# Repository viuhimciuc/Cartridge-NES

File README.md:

# 🎮 Nintendo Entertainment System (NES) Cartridge PCBs

An open-source collection of hardware design files and schematics for custom, functional **Nintendo Entertainment System (NES)** cartridge printed circuit boards (PCBs), using the [SST39SF010A](https://www.microchip.com/en-us/product/sst39sf010a), [SST39SF020A](https://www.microchip.com/en-us/product/sst39sf020a), [SST39SF040](https://www.microchip.com/en-us/product/sst39sf040) memory chip. This repository includes boards based on original discrete logic designs, advanced memory management controllers (MMCs), and mask ROM replacement utilities created inside **KiCad**.

---

## 📂 Repository Structure

The project organizes board designs by memory mapper architectures and utility profiles:

*   **📁 `Discrete logic boards using`** – Simple mapper solutions utilizing standard 74-series logic chips (e.g., AxROM, UxROM, NROM configurations).
*   **📁 `MMC1 boards NES-SxROM`** – Designs compatible with the Nintendo **MMC1** ASIC mapper family supporting multi-directional scrolling and battery-backed saves.
*   **📁 `MMC3 boards NES-TxROM`** – Performance configurations adapting the highly versatile **MMC3** ASIC architecture for scanline IRQ counters and larger ROM sizes.
*   **📁 `NES MASK ROM`** – Hardware breakout and adapter boards targeting pin-compatible conversions from modern Flash/EPROM/EEPROM chips to original NES hardware slots.
*   **📊 Documentation Assets:**
    *   `Mappers.xls` – Comparison matrices tracking hardware compatibility, signaling, and line configurations.
    *   `pin_MMC3.xls` – Precision mapping registers and Pinout details targeting the MMC3 layout.

---

## 📸 PCB Gallery

<p align="center">

</p>

---

## 🛠️ Getting Started & Manufacturing

### Prerequisites
1. Download and set up the stable branch of [KiCad EDA](https://kicad.org/).
2. Standard interactive hardware tools (soldering iron, multi-meter, flux).

### Cloning the Project
```bash
git clone https://github.com/viuhimciuc/Cartridge-NES.git
cd Cartridge-NES
```

### Exporting Gerbers for PCB Production
1. Launch **KiCad** and open the `.kicad_pcb` layout file from the directory matching your board configuration.
2. Navigate to **File** ➡️ **Plot...**
3. Select **Gerber** as the output configuration format.
4. Specify target layers (typically *F.Cu*, *B.Cu*, *F.Paste*, *B.Paste*, *F.Silkscreen*, *B.Silkscreen*, *F.Mask*, *B.Mask*, and *Edge.Cuts*).
5. Choose **Generate Drill Files...** using standard Exxon/Drill configurations.
6. Package all generated artifacts into a single `.zip` archive.
7. Upload the container directly to production fabs like [JLCPCB](https://jlcpcb.com/) or [PCBWay](https://www.pcbway.com/).

---

## 🤝 Contributing & Support

Contributions addressing trace corrections, optimized routing patterns, or alternative flash memory compatibility layouts are welcome! 

1. **Fork** this repository.
2. Build an active feature/fix branch (`git checkout -b feature/AmazingFeature`).
3. Commit structural modifications (`git commit -m 'Add support for unique flash footprints'`).
4. **Push** the configuration branch (`git push origin feature/AmazingFeature`).
5. Open a **Pull Request**.

---

## 📜 License

Distributed under the **MIT License**. Check out the accompanying `.gitignore` configuration for setup parameters.

---
<p align="center">Made with ❤️ for retro console preservation.</p>

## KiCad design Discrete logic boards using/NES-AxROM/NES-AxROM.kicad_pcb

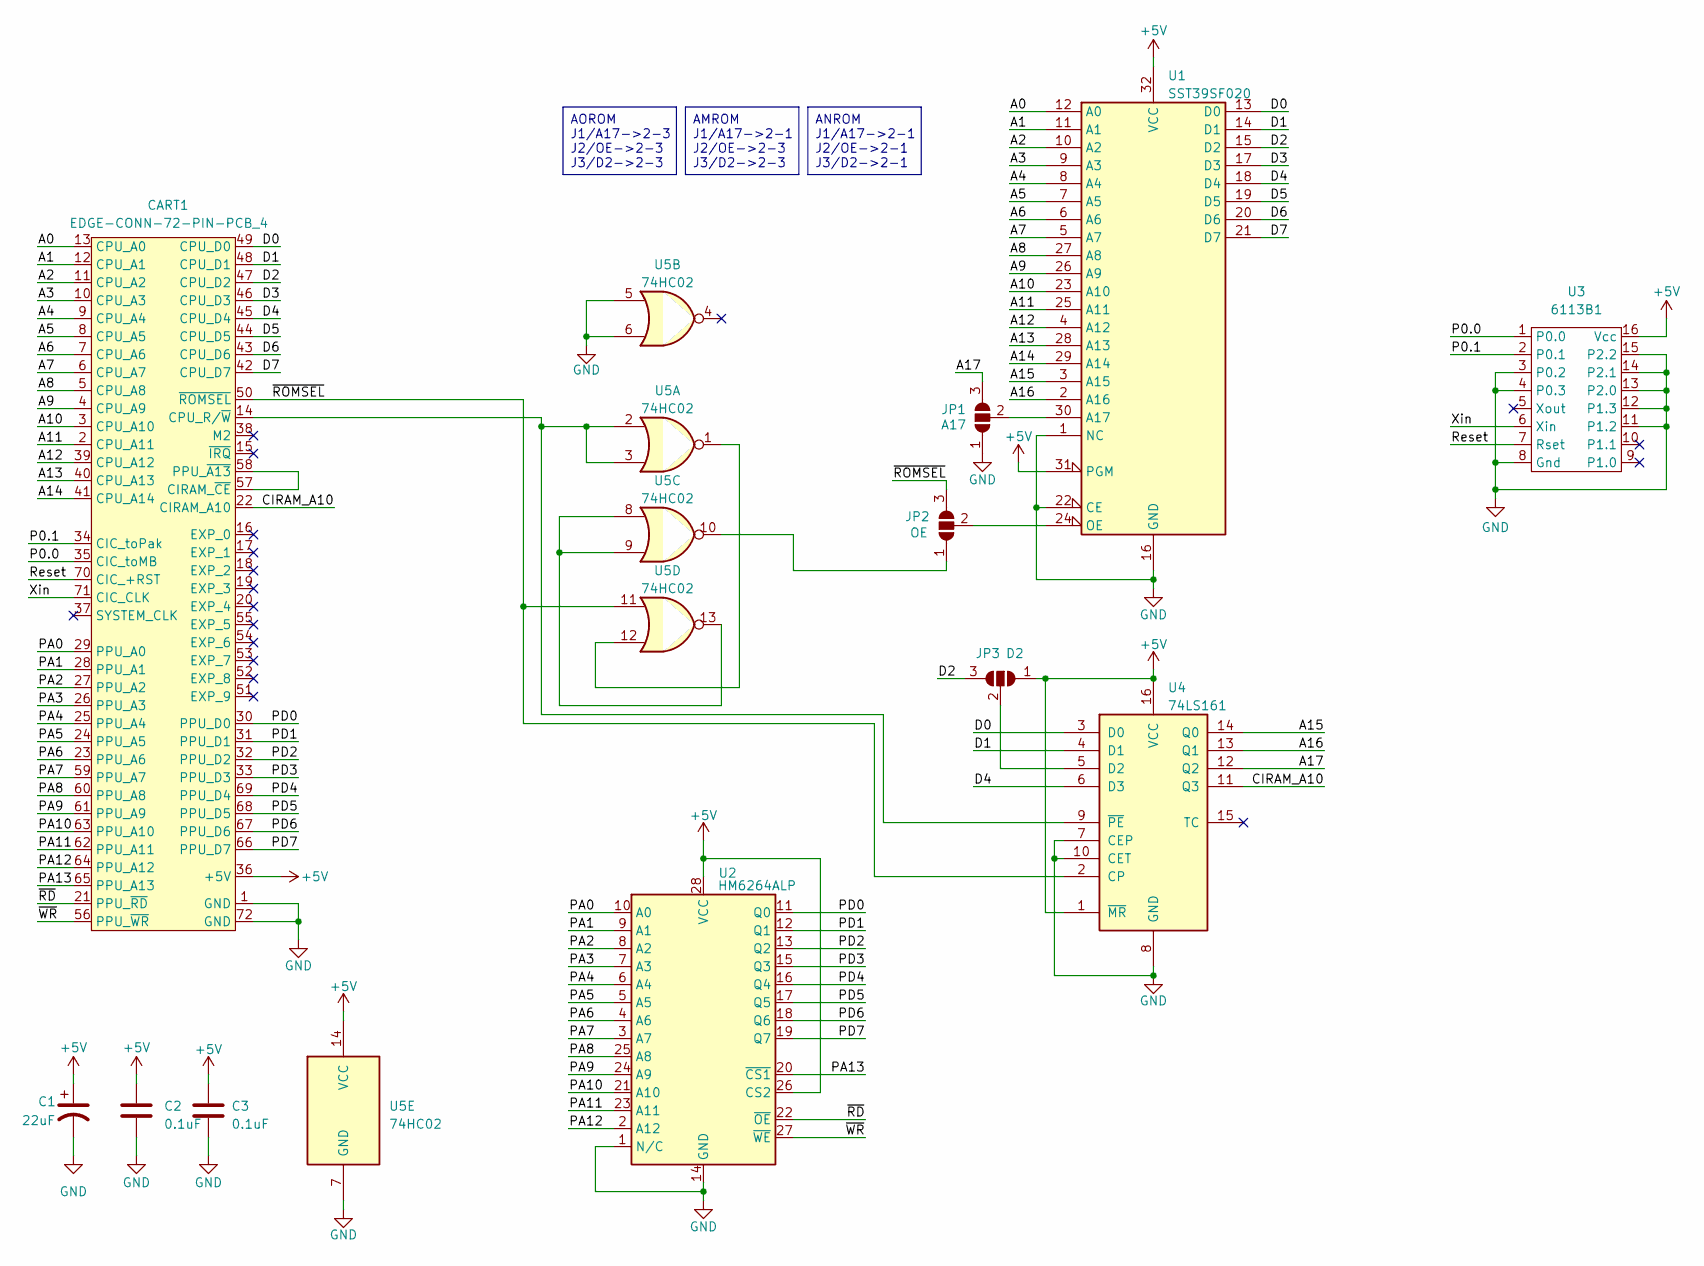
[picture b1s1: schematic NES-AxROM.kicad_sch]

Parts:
C1: 22uF; CP_Radial_D4.0mm_P2.00mm
C2, C3: 0.1uF; C_Axial_P7.5mm_P2.50mm
CART1: EDGE-CONN-72-PIN-PCB_4; PCB_4-CART-72-2.50-CONN
JP1: A17; SolderJumper-3_P1.3mm_Open_RoundedPad1.0x1.5mm_NumberLabels
JP2: OE; SolderJumper-3_P1.3mm_Open_RoundedPad1.0x1.5mm_NumberLabels
JP3: D2; SolderJumper-3_P1.3mm_Open_RoundedPad1.0x1.5mm_NumberLabels
U1: SST39SF020; DIP-32_W15.24mm
U2: HM6264ALP; DIP-28_W15.24mm
U3: 6113B1; DIP-16_W7.62mm
U4: 74LS161; DIP-16_W7.62mm
U5: 74HC02; DIP-14_W7.62mm

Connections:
+5V: C1.1, C2.1, C3.1, CART1.36 (+5V), JP3.1 (A), U1.31 (PGM), U1.32 (VCC), U2.26 (CS2), U2.28 (VCC), U3.16 (Vcc), U4.1 (~MR), U4.16 (VCC), U5.14 (VCC)
/A0: CART1.13 (CPU_A0), U1.12 (A0)
/A1: CART1.12 (CPU_A1), U1.11 (A1)
/A2: CART1.11 (CPU_A2), U1.10 (A2)
/A3: CART1.10 (CPU_A3), U1.9 (A3)
/A4: CART1.9 (CPU_A4), U1.8 (A4)
/A5: CART1.8 (CPU_A5), U1.7 (A5)
/A6: CART1.7 (CPU_A6), U1.6 (A6)
/A7: CART1.6 (CPU_A7), U1.5 (A7)
/A8: CART1.5 (CPU_A8), U1.27 (A8)
/A9: CART1.4 (CPU_A9), U1.26 (A9)
/A10: CART1.3 (CPU_A10), U1.23 (A10)
/A11: CART1.2 (CPU_A11), U1.25 (A11)
/A12: CART1.39 (CPU_A12), U1.4 (A12)
/A13: CART1.40 (CPU_A13), U1.28 (A13)
/A14: CART1.41 (CPU_A14), U1.29 (A14)
/A15: U1.3 (A15), U4.14 (Q0)
/A16: U1.2 (A16), U4.13 (Q1)
/A17: JP1.3 (B), U4.12 (Q2)
/CIRAM_A10: CART1.22 (CIRAM_A10), U4.11 (Q3)
/D0: CART1.49 (CPU_D0), U1.13 (D0), U4.3 (D0)
/D1: CART1.48 (CPU_D1), U1.14 (D1), U4.4 (D1)
/D2: CART1.47 (CPU_D2), JP3.3 (B), U1.15 (D2)
/D3: CART1.46 (CPU_D3), U1.17 (D3)
/D4: CART1.45 (CPU_D4), U1.18 (D4), U4.6 (D3)
/D5: CART1.44 (CPU_D5), U1.19 (D5)
/D6: CART1.43 (CPU_D6), U1.20 (D6)
/D7: CART1.42 (CPU_D7), U1.21 (D7)
/P0.0: CART1.35 (CIC_toMB), U3.1 (P0.0)
/P0.1: CART1.34 (CIC_toPak), U3.2 (P0.1)
/PA0: CART1.29 (PPU_A0), U2.10 (A0)
/PA1: CART1.28 (PPU_A1), U2.9 (A1)
/PA2: CART1.27 (PPU_A2), U2.8 (A2)
/PA3: CART1.26 (PPU_A3), U2.7 (A3)
/PA4: CART1.25 (PPU_A4), U2.6 (A4)
/PA5: CART1.24 (PPU_A5), U2.5 (A5)
/PA6: CART1.23 (PPU_A6), U2.4 (A6)
/PA7: CART1.59 (PPU_A7), U2.3 (A7)
/PA8: CART1.60 (PPU_A8), U2.25 (A8)
/PA9: CART1.61 (PPU_A9), U2.24 (A9)
/PA10: CART1.63 (PPU_A10), U2.21 (A10)
/PA11: CART1.62 (PPU_A11), U2.23 (A11)
/PA12: CART1.64 (PPU_A12), U2.2 (A12)
/PA13: CART1.65 (PPU_A13), U2.20 (~CS1)
/PD0: CART1.30 (PPU_D0), U2.11 (Q0)
/PD1: CART1.31 (PPU_D1), U2.12 (Q1)
/PD2: CART1.32 (PPU_D2), U2.13 (Q2)
/PD3: CART1.33 (PPU_D3), U2.15 (Q3)
/PD4: CART1.69 (PPU_D4), U2.16 (Q4)
/PD5: CART1.68 (PPU_D5), U2.17 (Q5)
/PD6: CART1.67 (PPU_D6), U2.18 (Q6)
/PD7: CART1.66 (PPU_D7), U2.19 (Q7)
/Reset: CART1.70 (CIC_+RST), U3.7 (Rset)
/Xin: CART1.71 (CIC_CLK), U3.6 (Xin)
/~RD: CART1.21 (PPU_~RD), U2.22 (~OE)
/~ROMSEL: CART1.50 (~ROMSEL), JP2.3 (B), U4.2 (CP), U5.11
/~WR: CART1.56 (PPU_~WR), U2.27 (~WE)
GND: C1.2, C2.2, C3.2, CART1.1 (GND), CART1.72 (GND), JP1.1 (A), U1.1 (NC), U1.16 (GND), U1.22 (CE), U2.1 (N/C), U2.14 (GND), U3.3 (P0.2), U3.4 (P0.3), U3.8 (Gnd), U3.11 (P1.2), U3.12 (P1.3), U3.13 (P2.0), U3.14 (P2.1), U3.15 (P2.2), U4.7 (CEP), U4.8 (GND), U4.10 (CET), U5.5, U5.6, U5.7 (GND)
unnamed: CART1.57 (CIRAM_~CE), CART1.58 (PPU_~A13)
unnamed: CART1.14 (CPU_R/~W), U4.9 (~PE), U5.2, U5.3
unnamed: JP1.2 (C), U1.30 (A17)
unnamed: JP2.1 (A), U5.10
unnamed: JP2.2 (C), U1.24 (OE)
unnamed: JP3.2 (C), U4.5 (D2)
unnamed: U5.1, U5.12
unnamed: U5.8, U5.9, U5.13

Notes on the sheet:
AMROM J1/A17->2-1 J2/OE->2-3 J3/D2->2-3
ANROM J1/A17->2-1 J2/OE->2-1 J3/D2->2-1
AOROM J1/A17->2-3 J2/OE->2-3 J3/D2->2-3

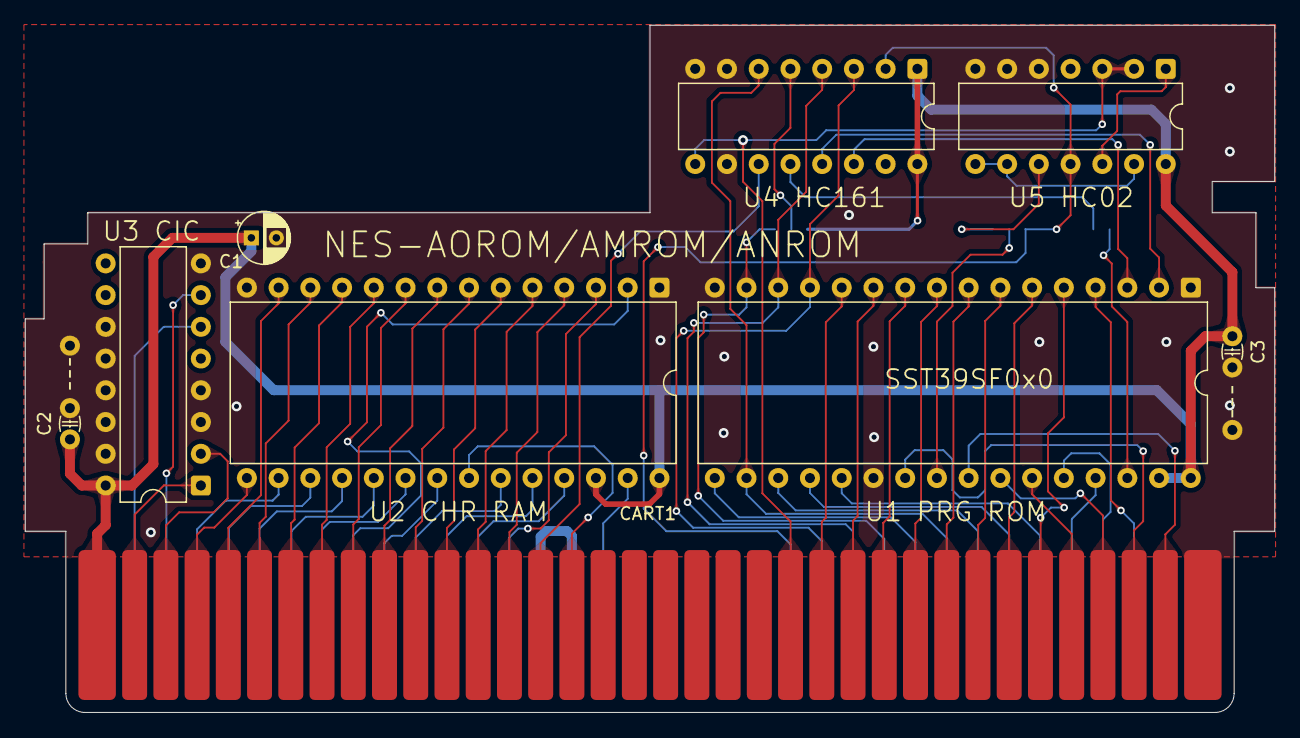
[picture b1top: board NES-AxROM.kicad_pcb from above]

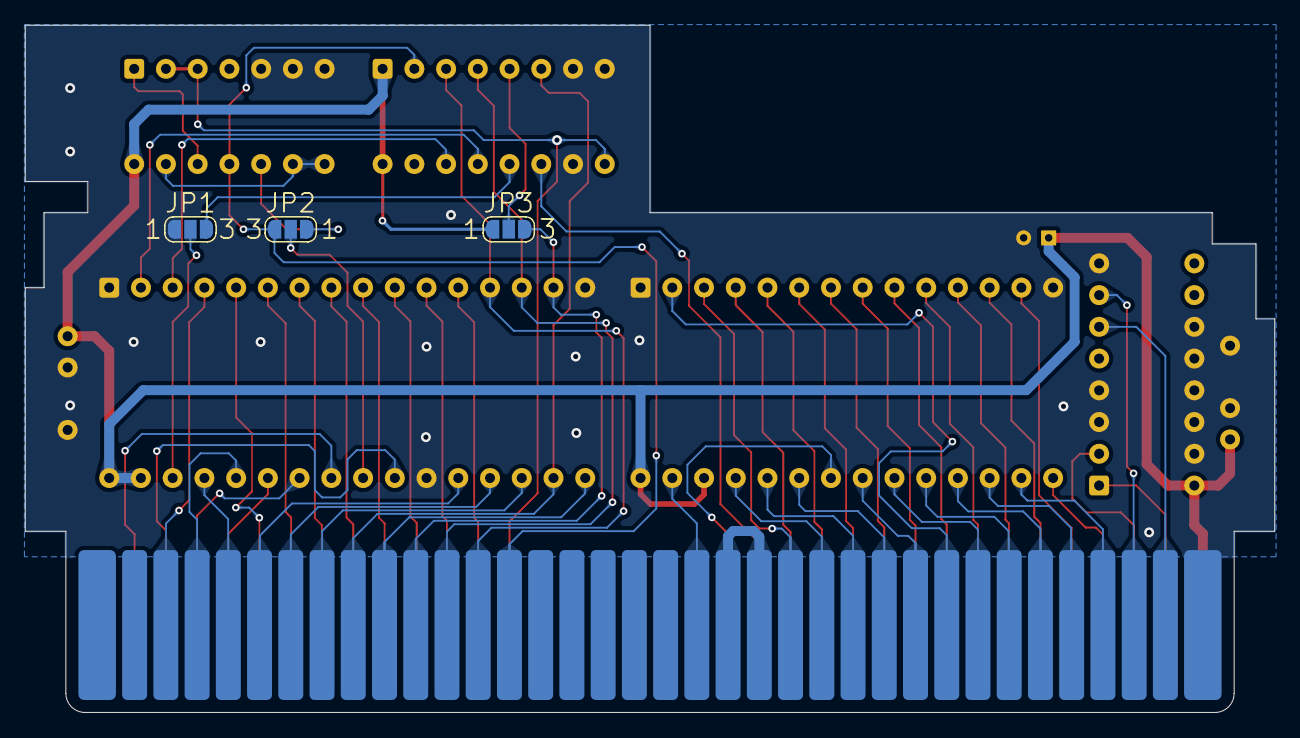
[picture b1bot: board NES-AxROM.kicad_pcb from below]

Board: 2 copper layers, 100.0 x 55.0 mm, 12 parts (3 on the bottom side), 66 nets.

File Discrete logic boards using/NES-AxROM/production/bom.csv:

Designator,Footprint,Quantity,Value,LCSC Part #
C1,CP_Radial_D4.0mm_P2.00mm,1,22uF,
"C2, C3",C_Axial_P7.5mm_P2.50mm,2,0.1uF,
CART1,PCB_4-CART-72-2.50-CONN,1,EDGE-CONN-72-PIN-PCB_4,
JP1,SolderJumper-3_P1.3mm_Open_RoundedPad1.0x1.5mm_NumberLabels,1,A17,
JP2,SolderJumper-3_P1.3mm_Open_RoundedPad1.0x1.5mm_NumberLabels,1,OE,
JP3,SolderJumper-3_P1.3mm_Open_RoundedPad1.0x1.5mm_NumberLabels,1,D2,
U1,DIP-32_W15.24mm,1,SST39SF020,
U2,DIP-28_W15.24mm,1,HM6264ALP,
U3,DIP-16_W7.62mm,1,6113B1,
U4,DIP-16_W7.62mm,1,74LS161,
U5,DIP-14_W7.62mm,1,74HC02,

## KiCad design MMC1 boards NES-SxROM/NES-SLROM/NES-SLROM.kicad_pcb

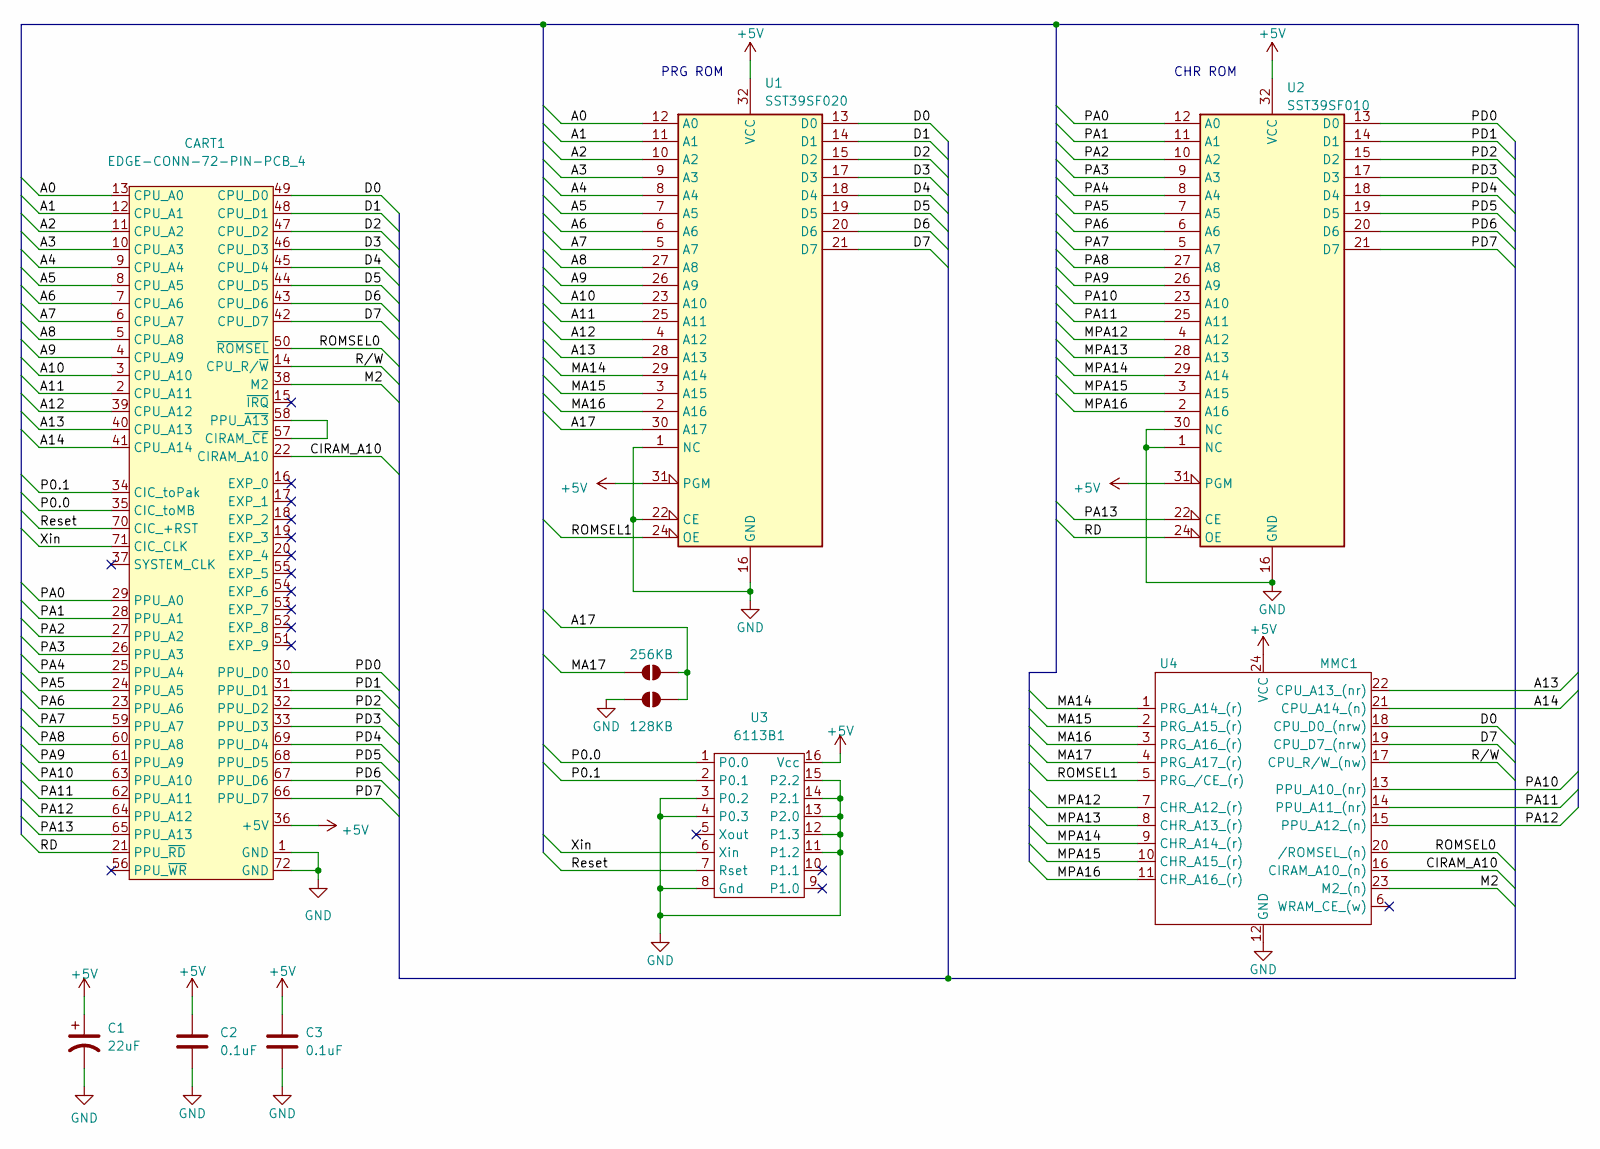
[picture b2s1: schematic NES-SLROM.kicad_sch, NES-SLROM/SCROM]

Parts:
C1: 22uF; CP_Radial_D4.0mm_P1.50mm
C2, C3: 0.1uF; C_Disc_D3.0mm_W1.6mm_P2.50mm
CART1: EDGE-CONN-72-PIN-PCB_4; PCB_4-CART-72-2.50-CONN
JP1: 256KB; SolderJumper-2_P1.3mm_Open_RoundedPad1.0x1.5mm
JP2: 128KB; SolderJumper-2_P1.3mm_Open_RoundedPad1.0x1.5mm
U1: SST39SF020; DIP-32_W15.24mm
U2: SST39SF010; DIP-32_W15.24mm
U3: 6113B1; DIP-16_W7.62mm
U4: MMC1; DIP-24_W7.62mm_Pads_1.78mm

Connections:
+5V: C1.1, C2.1, C3.1, CART1.36 (+5V), U1.31 (PGM), U1.32 (VCC), U2.31 (PGM), U2.32 (VCC), U3.16 (Vcc), U4.24 (VCC)
/A0: CART1.13 (CPU_A0), U1.12 (A0)
/A1: CART1.12 (CPU_A1), U1.11 (A1)
/A2: CART1.11 (CPU_A2), U1.10 (A2)
/A3: CART1.10 (CPU_A3), U1.9 (A3)
/A4: CART1.9 (CPU_A4), U1.8 (A4)
/A5: CART1.8 (CPU_A5), U1.7 (A5)
/A6: CART1.7 (CPU_A6), U1.6 (A6)
/A7: CART1.6 (CPU_A7), U1.5 (A7)
/A8: CART1.5 (CPU_A8), U1.27 (A8)
/A9: CART1.4 (CPU_A9), U1.26 (A9)
/A10: CART1.3 (CPU_A10), U1.23 (A10)
/A11: CART1.2 (CPU_A11), U1.25 (A11)
/A12: CART1.39 (CPU_A12), U1.4 (A12)
/A13: CART1.40 (CPU_A13), U1.28 (A13), U4.22 (CPU_A13_(nr))
/A14: CART1.41 (CPU_A14), U4.21 (CPU_A14_(n))
/A17: JP1.1 (A), JP2.1 (A), U1.30 (A17)
/CIRAM_A10: CART1.22 (CIRAM_A10), U4.16 (CIRAM_A10_(n))
/D0: CART1.49 (CPU_D0), U1.13 (D0), U4.18 (CPU_D0_(nrw))
/D1: CART1.48 (CPU_D1), U1.14 (D1)
/D2: CART1.47 (CPU_D2), U1.15 (D2)
/D3: CART1.46 (CPU_D3), U1.17 (D3)
/D4: CART1.45 (CPU_D4), U1.18 (D4)
/D5: CART1.44 (CPU_D5), U1.19 (D5)
/D6: CART1.43 (CPU_D6), U1.20 (D6)
/D7: CART1.42 (CPU_D7), U1.21 (D7), U4.19 (CPU_D7_(nrw))
/M2: CART1.38 (M2), U4.23 (M2_(n))
/MA14: U1.29 (A14), U4.1 (PRG_A14_(r))
/MA15: U1.3 (A15), U4.2 (PRG_A15_(r))
/MA16: U1.2 (A16), U4.3 (PRG_A16_(r))
/MA17: JP1.2 (B), U4.4 (PRG_A17_(r))
/MPA12: U2.4 (A12), U4.7 (CHR_A12_(r))
/MPA13: U2.28 (A13), U4.8 (CHR_A13_(r))
/MPA14: U2.29 (A14), U4.9 (CHR_A14_(r))
/MPA15: U2.3 (A15), U4.10 (CHR_A15_(r))
/MPA16: U2.2 (A16), U4.11 (CHR_A16_(r))
/P0.0: CART1.35 (CIC_toMB), U3.1 (P0.0)
/P0.1: CART1.34 (CIC_toPak), U3.2 (P0.1)
/PA0: CART1.29 (PPU_A0), U2.12 (A0)
/PA1: CART1.28 (PPU_A1), U2.11 (A1)
/PA2: CART1.27 (PPU_A2), U2.10 (A2)
/PA3: CART1.26 (PPU_A3), U2.9 (A3)
/PA4: CART1.25 (PPU_A4), U2.8 (A4)
/PA5: CART1.24 (PPU_A5), U2.7 (A5)
/PA6: CART1.23 (PPU_A6), U2.6 (A6)
/PA7: CART1.59 (PPU_A7), U2.5 (A7)
/PA8: CART1.60 (PPU_A8), U2.27 (A8)
/PA9: CART1.61 (PPU_A9), U2.26 (A9)
/PA10: CART1.63 (PPU_A10), U2.23 (A10), U4.13 (PPU_A10_(nr))
/PA11: CART1.62 (PPU_A11), U2.25 (A11), U4.14 (PPU_A11_(nr))
/PA12: CART1.64 (PPU_A12), U4.15 (PPU_A12_(n))
/PA13: CART1.65 (PPU_A13), U2.22 (CE)
/PD0: CART1.30 (PPU_D0), U2.13 (D0)
/PD1: CART1.31 (PPU_D1), U2.14 (D1)
/PD2: CART1.32 (PPU_D2), U2.15 (D2)
/PD3: CART1.33 (PPU_D3), U2.17 (D3)
/PD4: CART1.69 (PPU_D4), U2.18 (D4)
/PD5: CART1.68 (PPU_D5), U2.19 (D5)
/PD6: CART1.67 (PPU_D6), U2.20 (D6)
/PD7: CART1.66 (PPU_D7), U2.21 (D7)
/RD: CART1.21 (PPU_~RD), U2.24 (OE)
/ROMSEL0: CART1.50 (~ROMSEL), U4.20 (/ROMSEL_(n))
/ROMSEL1: U1.24 (OE), U4.5 (PRG_/CE_(r))
/Reset: CART1.70 (CIC_+RST), U3.7 (Rset)
/R/W: CART1.14 (CPU_R/~W), U4.17 (CPU_R/W_(nw))
/Xin: CART1.71 (CIC_CLK), U3.6 (Xin)
GND: C1.2, C2.2, C3.2, CART1.1 (GND), CART1.72 (GND), JP2.2 (B), U1.1 (NC), U1.16 (GND), U1.22 (CE), U2.1 (NC), U2.16 (GND), U2.30 (NC), U3.3 (P0.2), U3.4 (P0.3), U3.8 (Gnd), U3.11 (P1.2), U3.12 (P1.3), U3.13 (P2.0), U3.14 (P2.1), U3.15 (P2.2), U4.12 (GND)
unnamed: CART1.57 (CIRAM_~CE), CART1.58 (PPU_~A13)

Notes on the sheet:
PRG ROM
CHR ROM

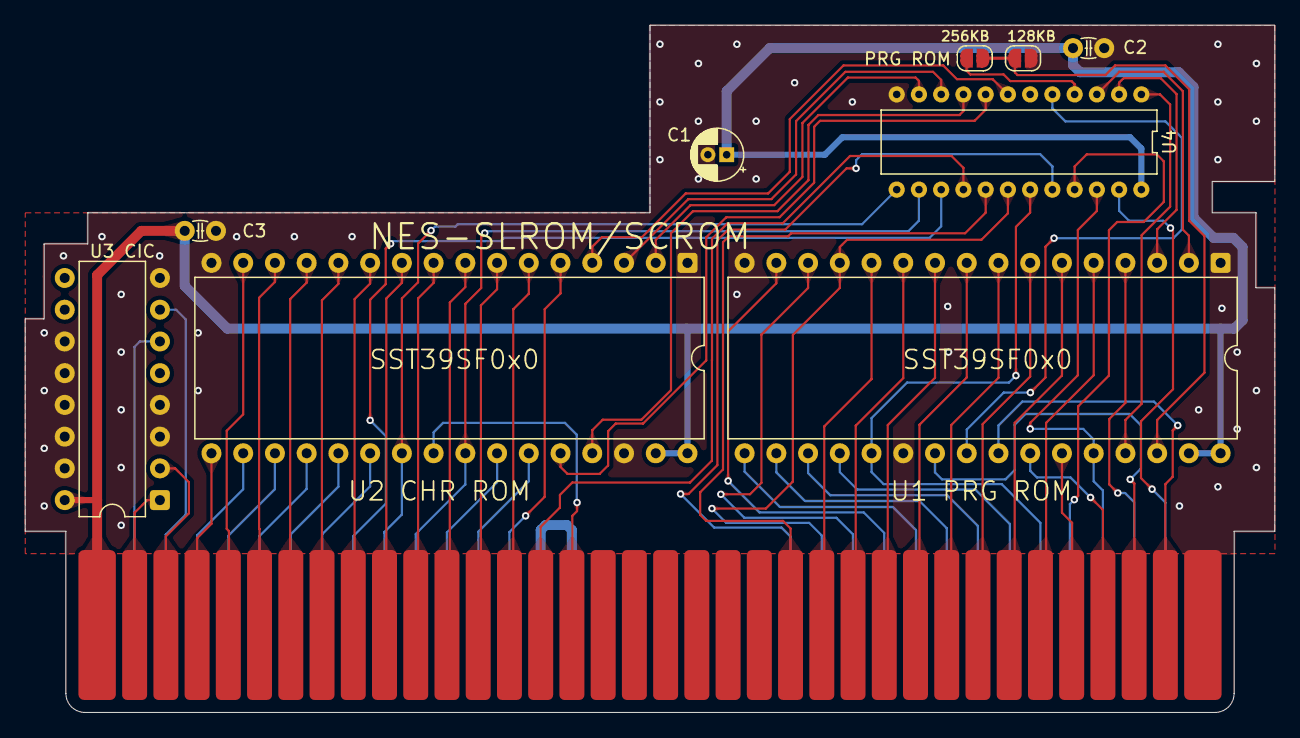
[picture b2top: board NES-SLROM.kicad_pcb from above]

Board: 2 copper layers, 100.0 x 55.0 mm, 10 parts (0 on the bottom side), 68 nets.

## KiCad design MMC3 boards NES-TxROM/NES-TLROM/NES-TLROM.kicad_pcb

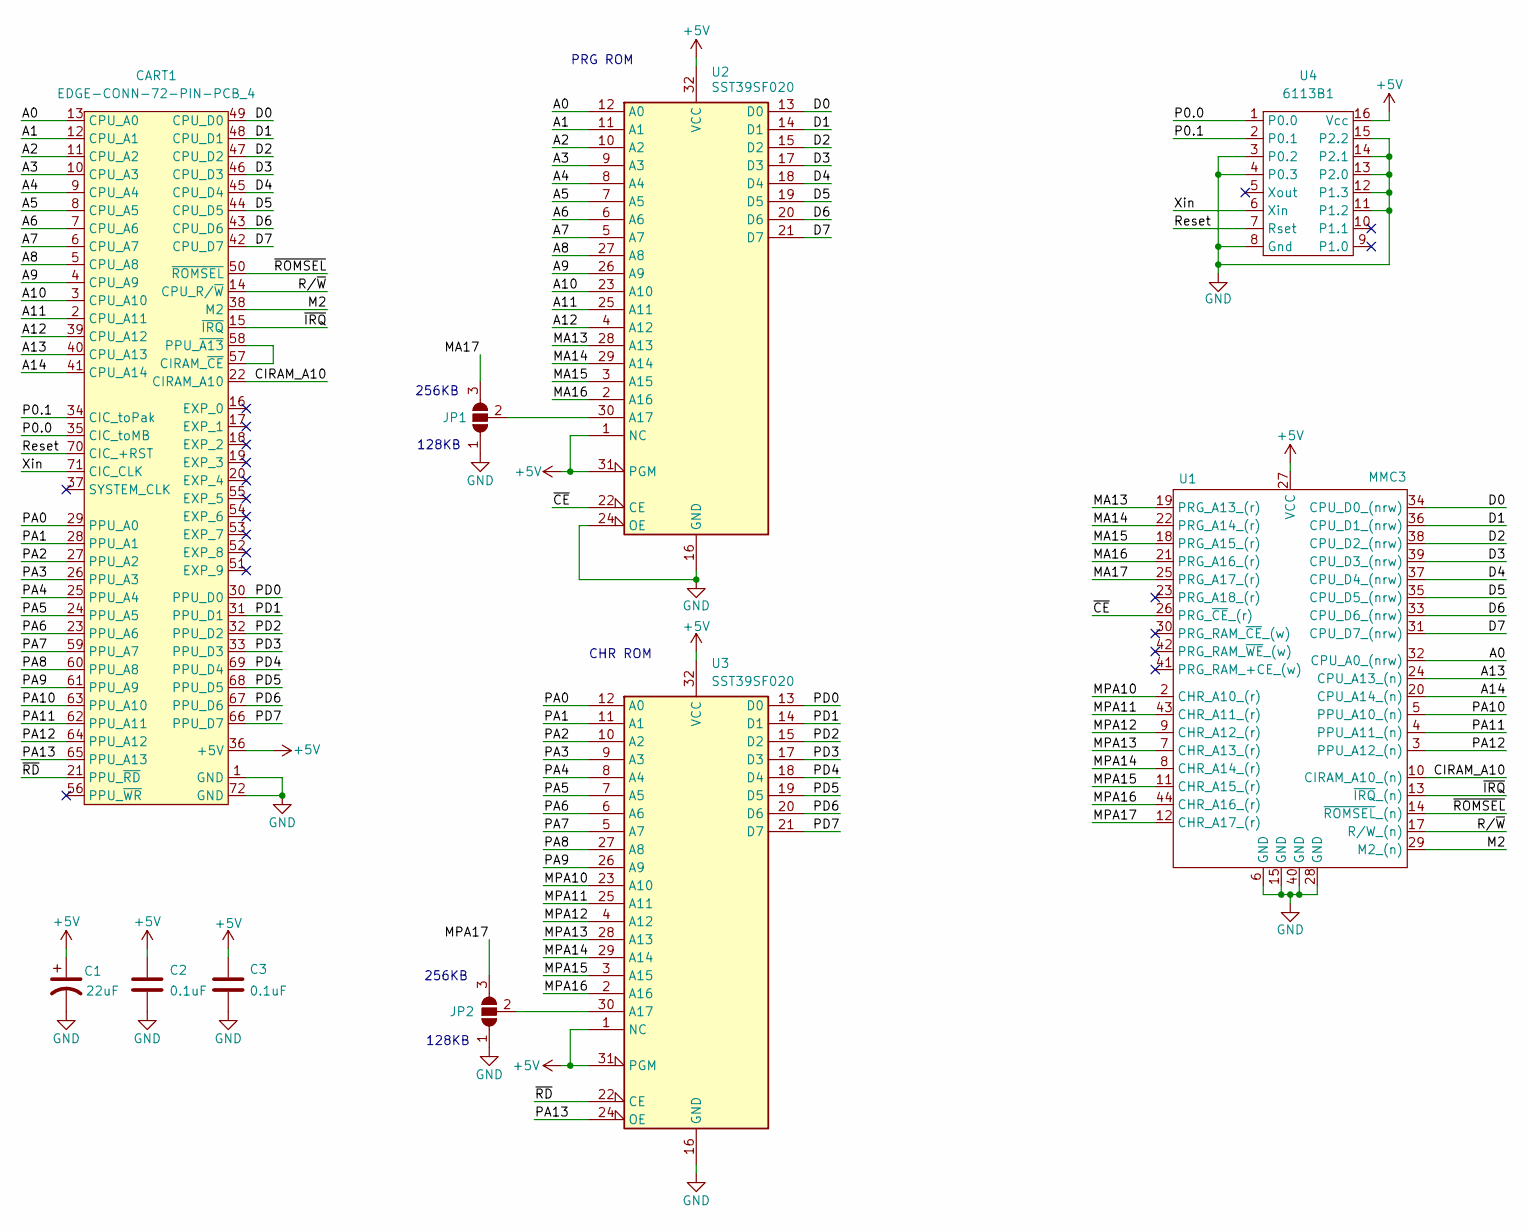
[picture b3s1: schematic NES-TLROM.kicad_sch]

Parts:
C1: 22uF; CP_Radial_D4.0mm_P2.00mm
C2, C3: 0.1uF; C_Axial_P7.5mm_P2.50mm
CART1: EDGE-CONN-72-PIN-PCB_4; PCB_4-CART-72-2.50-CONN
JP1, JP2: SolderJumper_3_Open; SolderJumper-3_P1.3mm_Open_RoundedPad1.0x1.5mm_NumberLabels
U1: MMC3; MMC3_TQFP-44
U2, U3: SST39SF020; DIP-32_W15.24mm
U4: 6113B1; DIP-16_W7.62mm

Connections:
+5V: C1.1, C2.1, C3.1, CART1.36 (+5V), U1.27 (VCC), U2.1 (NC), U2.31 (PGM), U2.32 (VCC), U3.1 (NC), U3.31 (PGM), U3.32 (VCC), U4.16 (Vcc)
/A0: CART1.13 (CPU_A0), U1.32 (CPU_A0_(nrw)), U2.12 (A0)
/A1: CART1.12 (CPU_A1), U2.11 (A1)
/A2: CART1.11 (CPU_A2), U2.10 (A2)
/A3: CART1.10 (CPU_A3), U2.9 (A3)
/A4: CART1.9 (CPU_A4), U2.8 (A4)
/A5: CART1.8 (CPU_A5), U2.7 (A5)
/A6: CART1.7 (CPU_A6), U2.6 (A6)
/A7: CART1.6 (CPU_A7), U2.5 (A7)
/A8: CART1.5 (CPU_A8), U2.27 (A8)
/A9: CART1.4 (CPU_A9), U2.26 (A9)
/A10: CART1.3 (CPU_A10), U2.23 (A10)
/A11: CART1.2 (CPU_A11), U2.25 (A11)
/A12: CART1.39 (CPU_A12), U2.4 (A12)
/A13: CART1.40 (CPU_A13), U1.24 (CPU_A13_(n))
/A14: CART1.41 (CPU_A14), U1.20 (CPU_A14_(n))
/CIRAM_A10: CART1.22 (CIRAM_A10), U1.10 (CIRAM_A10_(n))
/D0: CART1.49 (CPU_D0), U1.34 (CPU_D0_(nrw)), U2.13 (D0)
/D1: CART1.48 (CPU_D1), U1.36 (CPU_D1_(nrw)), U2.14 (D1)
/D2: CART1.47 (CPU_D2), U1.38 (CPU_D2_(nrw)), U2.15 (D2)
/D3: CART1.46 (CPU_D3), U1.39 (CPU_D3_(nrw)), U2.17 (D3)
/D4: CART1.45 (CPU_D4), U1.37 (CPU_D4_(nrw)), U2.18 (D4)
/D5: CART1.44 (CPU_D5), U1.35 (CPU_D5_(nrw)), U2.19 (D5)
/D6: CART1.43 (CPU_D6), U1.33 (CPU_D6_(nrw)), U2.20 (D6)
/D7: CART1.42 (CPU_D7), U1.31 (CPU_D7_(nrw)), U2.21 (D7)
/M2: CART1.38 (M2), U1.29 (M2_(n))
/MA13: U1.19 (PRG_A13_(r)), U2.28 (A13)
/MA14: U1.22 (PRG_A14_(r)), U2.29 (A14)
/MA15: U1.18 (PRG_A15_(r)), U2.3 (A15)
/MA16: U1.21 (PRG_A16_(r)), U2.2 (A16)
/MA17: JP1.3 (B), U1.25 (PRG_A17_(r))
/MPA10: U1.2 (CHR_A10_(r)), U3.23 (A10)
/MPA11: U1.43 (CHR_A11_(r)), U3.25 (A11)
/MPA12: U1.9 (CHR_A12_(r)), U3.4 (A12)
/MPA13: U1.7 (CHR_A13_(r)), U3.28 (A13)
/MPA14: U1.8 (CHR_A14_(r)), U3.29 (A14)
/MPA15: U1.11 (CHR_A15_(r)), U3.3 (A15)
/MPA16: U1.44 (CHR_A16_(r)), U3.2 (A16)
/MPA17: JP2.3 (B), U1.12 (CHR_A17_(r))
/P0.0: CART1.35 (CIC_toMB), U4.1 (P0.0)
/P0.1: CART1.34 (CIC_toPak), U4.2 (P0.1)
/PA0: CART1.29 (PPU_A0), U3.12 (A0)
/PA1: CART1.28 (PPU_A1), U3.11 (A1)
/PA2: CART1.27 (PPU_A2), U3.10 (A2)
/PA3: CART1.26 (PPU_A3), U3.9 (A3)
/PA4: CART1.25 (PPU_A4), U3.8 (A4)
/PA5: CART1.24 (PPU_A5), U3.7 (A5)
/PA6: CART1.23 (PPU_A6), U3.6 (A6)
/PA7: CART1.59 (PPU_A7), U3.5 (A7)
/PA8: CART1.60 (PPU_A8), U3.27 (A8)
/PA9: CART1.61 (PPU_A9), U3.26 (A9)
/PA10: CART1.63 (PPU_A10), U1.5 (PPU_A10_(n))
/PA11: CART1.62 (PPU_A11), U1.4 (PPU_A11_(n))
/PA12: CART1.64 (PPU_A12), U1.3 (PPU_A12_(n))
/PA13: CART1.65 (PPU_A13), U3.24 (OE)
/PD0: CART1.30 (PPU_D0), U3.13 (D0)
/PD1: CART1.31 (PPU_D1), U3.14 (D1)
/PD2: CART1.32 (PPU_D2), U3.15 (D2)
/PD3: CART1.33 (PPU_D3), U3.17 (D3)
/PD4: CART1.69 (PPU_D4), U3.18 (D4)
/PD5: CART1.68 (PPU_D5), U3.19 (D5)
/PD6: CART1.67 (PPU_D6), U3.20 (D6)
/PD7: CART1.66 (PPU_D7), U3.21 (D7)
/Reset: CART1.70 (CIC_+RST), U4.7 (Rset)
/R/~W: CART1.14 (CPU_R/~W), U1.17 (R/W_(n))
/Xin: CART1.71 (CIC_CLK), U4.6 (Xin)
/~CE: U1.26 (PRG_~CE_(r)), U2.22 (CE)
/~IRQ: CART1.15 (~IRQ), U1.13 (~IRQ_(n))
/~RD: CART1.21 (PPU_~RD), U3.22 (CE)
/~ROMSEL: CART1.50 (~ROMSEL), U1.14 (~ROMSEL_(n))
GND: C1.2, C2.2, C3.2, CART1.1 (GND), CART1.72 (GND), JP1.1 (A), JP2.1 (A), U1.6 (GND), U1.15 (GND), U1.28 (GND), U1.40 (GND), U2.16 (GND), U2.24 (OE), U3.16 (GND), U4.3 (P0.2), U4.4 (P0.3), U4.8 (Gnd), U4.11 (P1.2), U4.12 (P1.3), U4.13 (P2.0), U4.14 (P2.1), U4.15 (P2.2)
unnamed: CART1.57 (CIRAM_~CE), CART1.58 (PPU_~A13)
unnamed: JP1.2 (C), U2.30 (A17)
unnamed: JP2.2 (C), U3.30 (A17)

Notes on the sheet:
128KB
PRG ROM
CHR ROM
256KB

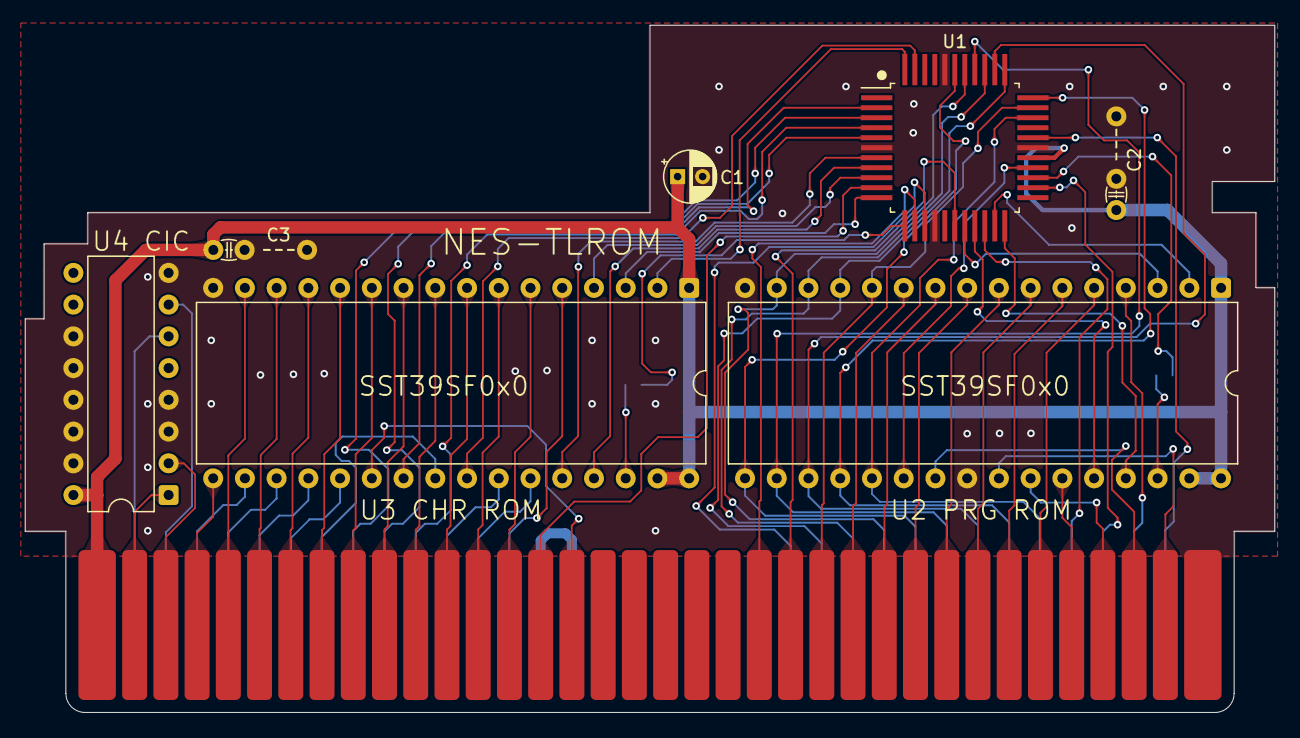
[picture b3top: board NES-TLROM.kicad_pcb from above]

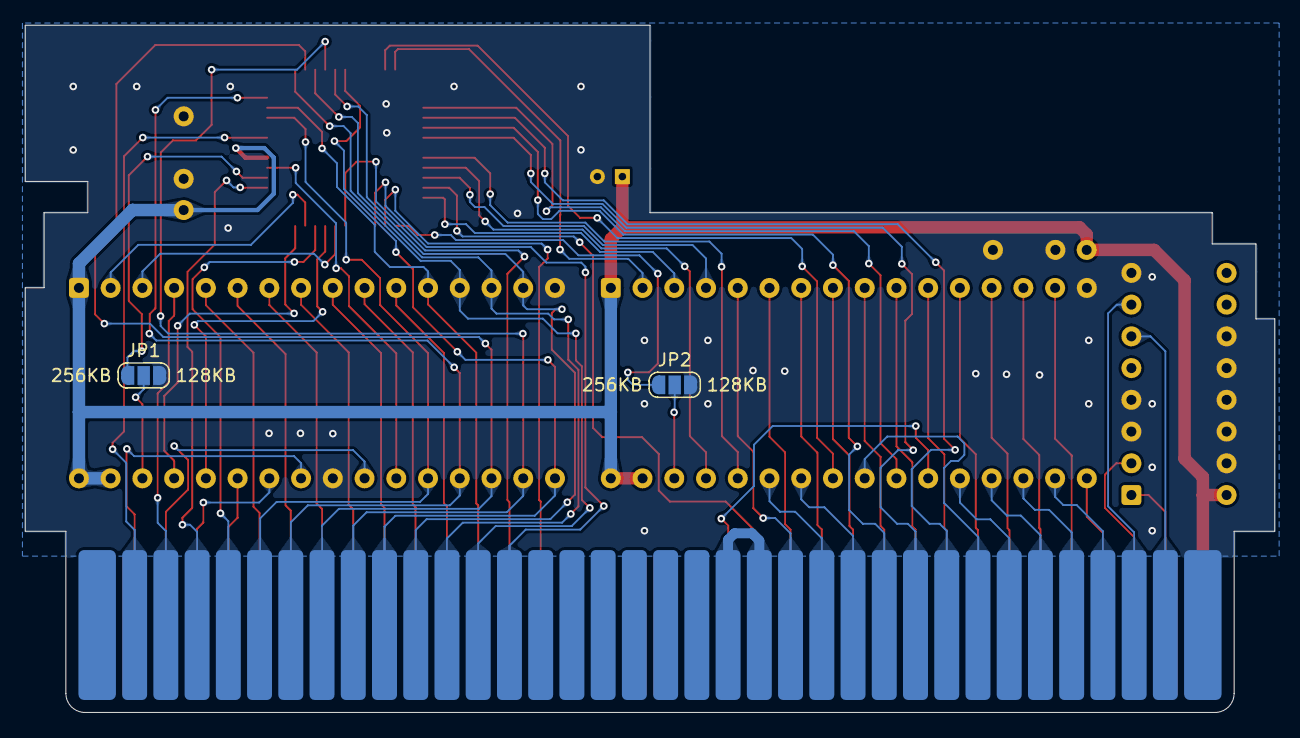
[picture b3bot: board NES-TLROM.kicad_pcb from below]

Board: 2 copper layers, 100.0 x 55.0 mm, 10 parts (2 on the bottom side), 74 nets.

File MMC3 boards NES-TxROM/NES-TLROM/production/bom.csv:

Designator,Footprint,Quantity,Value,LCSC Part #
C1,CP_Radial_D4.0mm_P2.00mm,1,22uF,
"C2, C3",C_Axial_P7.5mm_P2.50mm,2,0.1uF,
CART1,PCB_4-CART-72-2.50-CONN,1,EDGE-CONN-72-PIN-PCB_4,
U1,MMC3_TQFP-44,1,MMC3,
"U2, U3",DIP-32_W15.24mm,2,SST39SF020,
U4,DIP-16_W7.62mm,1,6113B1,

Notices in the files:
README.md:
License: MIT
